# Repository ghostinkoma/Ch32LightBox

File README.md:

# LightBox — CH32V003 LED Dimmer Controller

**English** · [日本語](README_JP.md)

> **Status: ✅ Hardware Verified & Operational (as of 2026-09, no issues)** — All functions confirmed on both custom PCB (KiCad) and universal breadboard/perfboard. Verified nightlight, brightness control, soft start/off, 12-hour endurance test, and virtually zero heat generation with a ~1A LED.
> **Enclosed and currently in actual use inside a 3D-printed case designed in Fusion 360.**
>
> **License: Non-Commercial (CC BY-NC 4.0 compliant / Attribution required, modification allowed for non-commercial use, provided AS-IS without warranty)** → [LICENSE](LICENSE)

A single-channel PWM LED dimmer controlled via a rotary encoder.
Powered by the **CH32V003** microcontroller with a self-contained firmware based on [ch32fun](https://github.com/cnlohr/ch32fun).

To prioritize reproducing brightness as **perceived by the human eye**, the PWM duty cycle is generated using the **CIE 1931 L\* (lightness) curve**. One click produces a "perceptually equal" shift in brightness—slower changes at low levels and sharper changes at high levels—achieving a balanced response for human vision.

## Key Features

| Feature | Description |
|---|---|
| **CIE L\* Dimming** | Perceptually uniform brightness. 64 total steps, LUT generated at startup, runtime lookup via integer table. |
| **16-bit PWM** | TIM2, default 4095 steps / ~12 kHz. Adjustable resolution and frequency in `config.h`. |
| **Debouncing** | Full-step state machine (Ben Buxton) + direction reversal lockout (default 5 ms). No simple delays used. |
| **Fast-turn Snap** | Immediately sets duty to 100% or 0% if turned in the same direction $j$ times within $n$ ms. |
| **CW/CCW Support** | Swap rotation direction with a single line in `config.h`. |
| **Brightness Memory** | Flash wear leveling (dedicated 2 KB area, saved after 5 sec, ~1024x lifespan extension, saves ON/OFF state). |
| **Overheat Failsafe** (Default OFF) | Forcefully shuts off main PWM (MOSFET) when overheated → resumes when cooled down. Thermal throttles to $j$\% after $n$ cycles. **Die estimation disabled due to false triggers (`TEMP_PROTECT_ENABLE 0`)**; enable only when using an external NTC sensor. |
| **Watchdog** | IWDG. Automatically resets on system freeze for self-recovery. |
| **EMI Mitigation** | Configurable PWM slew rate (GPIO speed) + spread spectrum (period dithering, brightness invariant). |
| **Nightlight (WS2812 or single LED)** | When completely dark: ①WS2812/SK6812 breathes light↔dark on the CIE curve (RGB/RGBW, color order, max color), or ②a single-color LED blinks `x` ms every `n` s. |
| **Deep Low-Power (experimental)** | Optional battery mode (`LOW_POWER_MODE`): single-LED nightlight with the MCU in Standby between blinks (AWU periodic wake, push-switch EXTI wake). Default off; see CONFIG_REFERENCE. |
| **Soft Start** | Smoothly fades in/out to target brightness on power ON/OFF based on CIE curve (duration set in config, disabled if 0, max 65535 ms). |
| **Push Switch** | Short press toggles ON/OFF (time-based debouncing; smoothly tracks re-triggering during active fades). |

All configuration options are centralized in **`source/config.h`** (see [CONFIG_REFERENCE.md](documents/CONFIG_REFERENCE.md) for details).
Detailed specifications are in [SPEC.md](documents/SPEC.md), design decisions are in [DESIGN.md](documents/DESIGN.md), and battery / low-power and LED-driver notes are in [POWER_AND_DRIVER.md](documents/POWER_AND_DRIVER.md).

## Pinout (**All features fit on SOP8 / J4M6**)

| Pin | Signal | Function |
|---|---|---|
| PA1 | ENC_A | Encoder Phase A (Internal pull-up, Common=GND) |
| PC1 | ENC_B | Encoder Phase B (Internal pull-up, Common=GND) |
| PA2 | ENC_SW | Push Switch (Internal pull-up, Active Low) |
| PC2 | PWM | **Main LED Output** (default `PWM_PIN`=PC2 → TIM2_CH2 remap1) |
| PC4 | (Selectable) | **WS2812 Nightlight** / External Temp Sensor / Warning LED (Mutually exclusive, choose one) |
| PD1 | SWIO | Programming / debugprintf (Reserved) |

> **Feature ↔ pin assignment is done entirely in `config.h`** (one pin macro per feature: `PWM_PIN`, `ENC_*_PIN`, `WS_DIN_PIN`, `TEMP_SENSE_PIN`, `WARN_LED_PIN`). `source/pins.h` validates capabilities (PWM-/ADC-capable pins) and pin conflicts at compile time, and the LightBox Studio config editor mirrors the same checks. See the “Feature ↔ Pin Assignment” section of [CONFIG_REFERENCE.md](documents/CONFIG_REFERENCE.md).

> **Temperature protection is OFF by default** (die estimation rejected due to false shutdowns). Watchdog and EMI mitigations **require no external pins**, allowing PC4—the only remaining free pin on SOP8—to be used for the nightlight.
> If an external physical temperature sensor or warning LED is needed, allocate PC4 accordingly (mutually exclusive with the nightlight). To use more features simultaneously, switch to TSSOP20/QFN (F4P6) and assign individual pins in `config.h`.

## Connecting the LED

- **Recommended**: PC2 → MOSFET gate (e.g., AO3400 / 2N7002), driving the LED on the low side via the drain.
- **Simplified**: Low-current LEDs can be connected directly via `PC2 → [Resistor] → LED → GND` (Strictly respect $I_{\max} \approx 8\text{ mA}$ per pin).
- **Overheat Protection (Default OFF)**: The CH32V003 lacks an internal die temperature sensor. The initial duty-based "die temperature estimation" caused **false shutdowns (sudden turn-offs during continuous use)** because it was not a physical measurement. It has been **rejected (`TEMP_PROTECT_ENABLE 0`)**. If physical thermal protection is strictly required, attach a thermal-coupled NTC on the MOSFET to an ADC pin and run with `TEMP_PROTECT_ENABLE=1` + `TEMP_SOURCE=EXTERNAL`. See SPEC.md for details.

## Operation

- **Rotate Encoder**: $\pm 1$ step per click (perceptually equal spacing using CIE L*).
- **Fast Turn** (Default: 6+ clicks within 0.5s): Snaps to full brightness (100%) in the bright direction, or turns off (0%) in the dark direction.
- **Push Switch Short Press**: Toggles ON/OFF (retains last brightness level).
- **Auto Memory**: Defaults to 0 on first boot. Setting a brightness and leaving it untouched for 5 seconds automatically saves it to flash for next startup restoration.
- **Soft Start**: Fades in/out smoothly to target brightness on power ON/OFF or boot up (fade duration configured in config).
- **Nightlight**: Breathes automatically when turned completely dark (turns off when main LED turns on/brightens).

## Build & Flash

### ① ch32fun + Makefile (Verified Standard Build)

Dependencies: [ch32fun](https://github.com/cnlohr/ch32fun), RISC-V GCC (xpack riscv-none-elf recommended for `rv32ec libgcc`), WCH-LinkE.

```bash
cd source
make lightbox.bin CH32FUN=/path/to/ch32fun/ch32fun    # Build only
make             CH32FUN=/path/to/ch32fun/ch32fun    # Build -> Flash
```

Build memory footprints (Default config, all features ON, `DEBUG_LOG=0`): **Flash 8200 B / 16 KB (50%), RAM 184 B (9%)**.
Stripped footprint: Core only ~3 KB, + Nightlight ~3.6 KB. `DEBUG_LOG=1` adds ~1 KB.

> Set `DEBUG_LOG` to 1 only during development. `printf` is blocking and can stall if an SWD host is disconnected, causing dropped inputs in hot loops. Defaults to 0, which unlinks the printf infrastructure entirely.

### ② PlatformIO

See [PLATFORMIO.md](PLATFORMIO.md) (`platformio.ini` included).
*Note: The PlatformIO build has not been verified in this environment. The verified build method is the Makefile above.*

### ③ LightBox Studio (GUI — no VS Code required)

For a GUI-only workflow (`config.h` editing → compile → flash from a single menu), use the Java toolset in [tools/LightBoxStudio/](tools/LightBoxStudio/README.md). It downloads a self-contained toolchain on first run, so no command line or VS Code is required. See the [LightBox Studio README](tools/LightBoxStudio/README.md) for details.

## Directory Structure

```
LightBox/
├─ source/         Firmware source files
│  ├─ lightbox.c      Main application (main / encoder / PWM)
│  ├─ config.h        Centralized configuration (edit parameters here)
│  ├─ cie.h           CIE L* curve library (shared by main PWM & nightlight)
│  ├─ store.h         Non-volatile brightness storage (wear leveling)
│  ├─ temp.h          Temperature reading (external NTC, default OFF)
│  ├─ wdt.h           Watchdog timer (IWDG)
│  ├─ nightlight.h    WS2812/SK6812 nightlight driver
│  ├─ funconfig.h     ch32fun environment configuration
│  └─ Makefile
├─ documents/      SPEC.md / CONFIG_REFERENCE.md / HARDWARE.md / DESIGN.md / POWER_AND_DRIVER.md (+ *_JP.md)
├─ tools/          LightBoxStudio/ = GUI toolset (config edit → build → flash, no VS Code)
├─ ldscript/       Linker script for PlatformIO (lightbox_ch32v003.ld)
├─ PCB/            KiCad board files (LightBox/ = Schematic/PCB; AertWork.png; KiCad/ = FDS5680 lib)
├─ platformio.ini / PLATFORMIO.md
├─ 3D_Models/      Enclosure (Fusion 360 design / STL files, 3D printed)
└─ LICENSE         Non-commercial license (CC BY-NC 4.0 compliant)
```

## Enclosure

**Designed in Fusion 360 → 3D printed**. The board is assembled inside and **currently in operational use** (STL files available in `3D_Models/`).

## Hardware (PCB)

PCB layout, schematic, and artwork (with pin headers) completed → `PCB/LightBox/` (KiCad).
**Pin routing matches firmware exactly.** Details, BOM, and J1 pinout are in [HARDWARE.md](documents/HARDWARE.md).

- U1 CH32V003 (SOP8) / Q1 FDS5680 (N-MOSFET, low-side drive for main LED) / D1 SK6812 (OST45050C1A-W nightlight)
- R1 $100\ \Omega$ (Gate series resistor) / R2 $10\text{ k}\Omega$ (Gate pull-down = LED OFF during reset) / **D2 Pilot LED + R3 $100\ \Omega$ (series)**
- **Main (Power) LED is off-board** (Connected via LED OUT → J1). **Near-zero heat generation with ~1A LED** (heatsink added only as a precaution).
- J1 9-pin header: Breaks out Power / SWIO / Encoder / Signals for both LEDs. **Powered by $\text{VDD} = 5\text{ V}$**.
- Equivalent circuit constructed on a 1.27 mm pitch universal perfboard and verified working.

## Verification Status — ✅ Hardware Verified (Running Continuously)

- **★ Physical Board Operation Confirmed (2026-09-16 ~ present, running without issues)**: Board schematic/routing verified, flashing successful.
  - **Nightlight** (SK6812 / OST45050C1A-W, RGBW sequence)
  - **Brightness adjustment** (CIE L*, acceleration x3, fast-turn snap)
  - **ON/OFF soft start & soft off**
  - **12-hour ON / 12-hour OFF endurance test passed** (Disabling thermal protection eliminated false cutoffs, ensuring long-term stability)
- Build checks: Zero compiler warnings across all feature ON/OFF, RGBW, and half-step combinations (Makefile, ch32fun).
- Host simulation tests: CIE LUT, encoder state machine, flash wear store boundaries, nightlight curves, color ordering, acceleration, thermal model.
- Unverified: Long-term Flash wear (~10 million cycles by design), external NTC thermal protection (disabled by default), PlatformIO build environment.

## License

This project (original parts of firmware, PCB, enclosure, and documentation created by ghostinkoma) is licensed under a **Non-Commercial License (Creative Commons Attribution-NonCommercial 4.0 International / CC BY-NC 4.0 compliant)**. See [LICENSE](LICENSE) for full details.

- **Non-Commercial Use Only** (Contact the author for commercial licensing).
- **Attribution Required** (Must credit the original author **ghostinkoma** and "LightBox").
- **Modifications Allowed** (Free to adapt for non-commercial purposes; derivative works must inherit the same license conditions).
- **No Warranty / No Liability** (Provided "AS IS". The author accepts no responsibility for damages resulting from use).

*Note: Bundled/dependent third-party code (e.g., [ch32fun](https://github.com/cnlohr/ch32fun)) remains under its respective original licenses (MIT-x11 / NewBSD).*

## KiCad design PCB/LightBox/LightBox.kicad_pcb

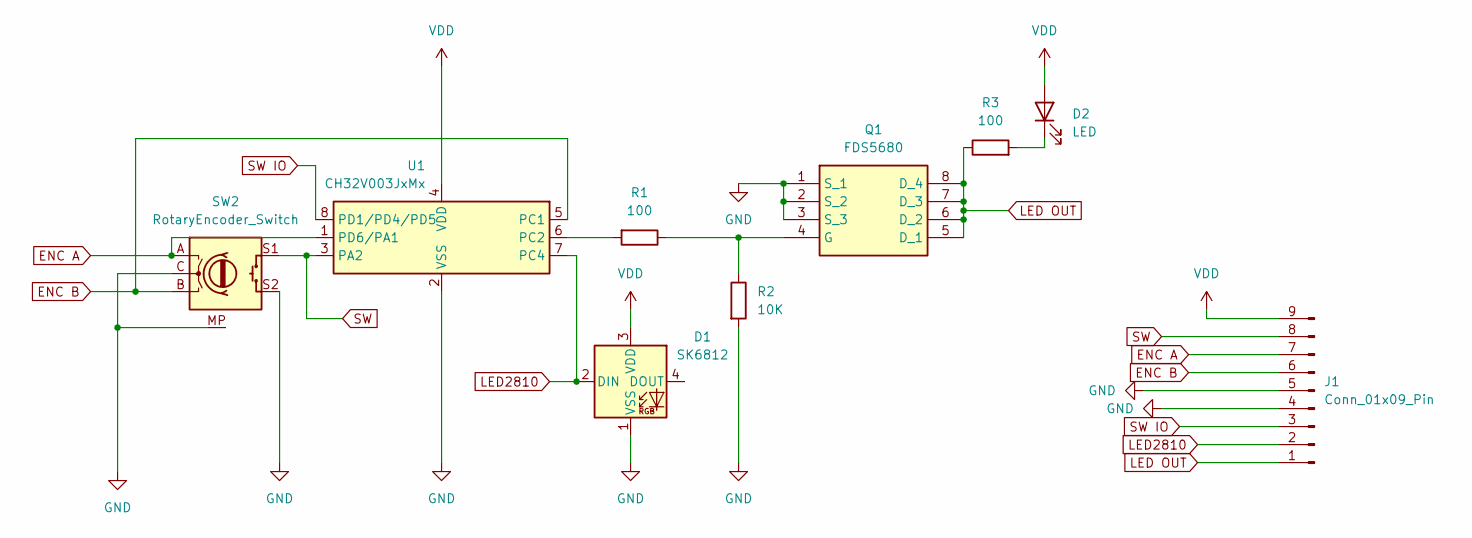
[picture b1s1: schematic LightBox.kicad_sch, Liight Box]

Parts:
D1: SK6812; LED_SK6812_PLCC4_5.0x5.0mm_P3.2mm
D2: LED; LED_D3.0mm
J1: Conn_01x09_Pin; PinHeader_1x09_P2.54mm_Vertical
Q1: FDS5680; SOIC-8-1EP_3.9x4.9mm_P1.27mm_EP2.29x3mm; Manufacturer_Part_Number FDS5680; Mouser Part Number 512-FDS5680
R1, R3: 100; R_0201_0603Metric
R2: 10K; R_0201_0603Metric
SW2: RotaryEncoder_Switch; RotaryEncoder_Alps_EC11E-Switch_Vertical_H20mm
U1: CH32V003JxMx; SOP-8_3.9x4.9mm_P1.27mm

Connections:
ENC A: J1.7, SW2.A, U1.1 (PD6/PA1)
ENC B: J1.6, SW2.B, U1.5 (PC1)
GND: D1.1 (VSS), J1.4, J1.5, Q1.1 (S_1), Q1.2 (S_2), Q1.3 (S_3), R2.2, SW2.C, SW2.MP, SW2.S2, U1.2 (VSS)
LED2810: D1.2 (DIN), J1.2, U1.7 (PC4)
LED OUT: J1.1, Q1.5 (D_1), Q1.6 (D_2), Q1.7 (D_3), Q1.8 (D_4), R3.1
unnamed: D2.1 (K), R3.2
unnamed: Q1.4 (G), R1.1, R2.1
unnamed: R1.2, U1.6 (PC2)
SW: J1.8, SW2.S1, U1.3 (PA2)
SW IO: J1.3, U1.8 (PD1/PD4/PD5)
VDD: D1.3 (VDD), D2.2 (A), J1.9, U1.4 (VDD)

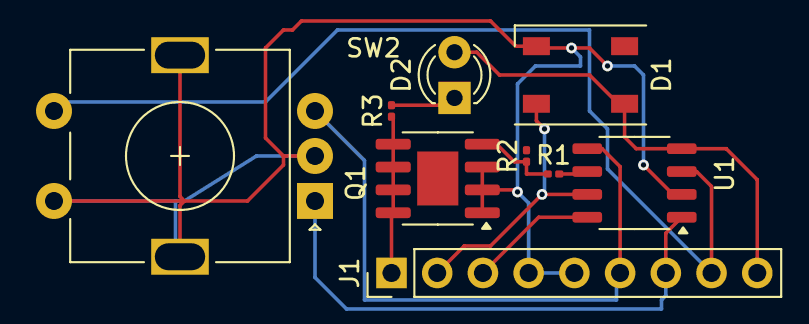
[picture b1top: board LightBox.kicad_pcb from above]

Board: 2 copper layers, 9 parts (0 on the bottom side), 11 nets.

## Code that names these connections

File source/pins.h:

/*
 * pins.h — 機能↔ピン割当の能力モデル・導出・コンパイル時検証 (CH32V003 SOP8 / J4M6)
 *
 *  config.h の「1機能=1ピンマクロ」から、各機能に必要な低レベル情報
 *  (GPIOポート/ピン番号 / ADCチャネル / PWMのタイマ・チャネル・remap) を導出し、
 *  ハード能力違反(PWM/ADC不可ピン)とピン衝突(2機能が同一ピン)をコンパイル時に弾く。
 *
 *  ── SOP8 (J4M6) の実在ピンと能力 ──  (出典: CH32V003 データシート / ch32fun ch32v003hw.h)
 *   pin   GPIO      ADCch   PWM経路(正出力)            既定用途
 *   PA1   GPIOA/1   1       TIM1_CH2 (no remap)        ENC_A
 *   PA2   GPIOA/2   0       (CH2N=相補のみ→PWM非対応)   ENC_SW
 *   PC1   GPIOC/1   -       TIM2_CH4 (remap1)          ENC_B
 *   PC2   GPIOC/2   -       TIM2_CH2 (remap1) ★既定PWM
 *   PC4   GPIOC/4   2       TIM1_CH4 (no remap)        常夜灯/温度/警告灯
 *   PD1   GPIOD/1   -       (CH3N=相補のみ) ※SWIO=書込/printf 予約
 *
 *  ※既定構成(PWM=PC2)は従来と同一のレジスタ操作を生成する(挙動不変)。
 *    PC2 以外の PWM ピンは「コンパイル対応・実機未検証」。
 */
#ifndef PINS_H
#define PINS_H

#include "ch32fun.h"   /* ピンマクロ(PA1=1,PC2=34,…) / GpioOf / TIM/RCC/AFIO 定義 */
#include "config.h"    /* 機能↔ピンの割当・有効フラグ */

/* ch32fun のピンマクロは整数値: 汎用の導出はビット演算で行える。
 *   GPIOポート = GpioOf(pin)  (= GPIOA_BASE + 0x400*(pin>>4))
 *   ピン番号   = (pin & 0x7)   (SOP8 は全て 0..7) */
#define LB_GPIO_OF(pin)   GpioOf(pin)
#define LB_PINNUM_OF(pin) ((pin) & 0x7)

/* SOP8 実在ピンか (それ以外は物理的に存在しない) */
#define LB_PIN_IS_SOP8(p) \
    ((p)==PA1 || (p)==PA2 || (p)==PC1 || (p)==PC2 || (p)==PC4 || (p)==PD1)

/* =========================================================================
 *  PWM 出力ピン → タイマ / チャネル / remap の導出
 *  正出力(単出力)チャネルのみ対応。相補(PA2=CH2N/PD1=CH3N)は既定除外。
 * ========================================================================= */
#if   PWM_PIN == PC2
  #define PWM_USES_TIM1    0
  #define PWM_CH           2
  #define PWM_REMAP_CLEAR  AFIO_PCFR1_TIM2_REMAP
  #define PWM_REMAP_SET    AFIO_PCFR1_TIM2_REMAP_PARTIALREMAP1
  #define PWM_RCC_GPIO_BIT RCC_APB2Periph_GPIOC
#elif PWM_PIN == PC1
  #define PWM_USES_TIM1    0
  #define PWM_CH           4
  #define PWM_REMAP_CLEAR  AFIO_PCFR1_TIM2_REMAP
  #define PWM_REMAP_SET    AFIO_PCFR1_TIM2_REMAP_PARTIALREMAP1
  #define PWM_RCC_GPIO_BIT RCC_APB2Periph_GPIOC
#elif PWM_PIN == PA1
  #define PWM_USES_TIM1    1
  #define PWM_CH           2
  #define PWM_REMAP_CLEAR  AFIO_PCFR1_TIM1_REMAP
  #define PWM_REMAP_SET    AFIO_PCFR1_TIM1_REMAP_NOREMAP
  #define PWM_RCC_GPIO_BIT RCC_APB2Periph_GPIOA
#elif PWM_PIN == PC4
  #define PWM_USES_TIM1    1
  #define PWM_CH           4
  #define PWM_REMAP_CLEAR  AFIO_PCFR1_TIM1_REMAP
  #define PWM_REMAP_SET    AFIO_PCFR1_TIM1_REMAP_NOREMAP
  #define PWM_RCC_GPIO_BIT RCC_APB2Periph_GPIOC
#else
  #error "PWM_PIN は PWM 可能な SOP8 ピンにしてください: PC2(TIM2_CH2)/PC1(TIM2_CH4)/PA1(TIM1_CH2)/PC4(TIM1_CH4)"
#endif

#if PWM_USES_TIM1
  #define PWM_TIMREG TIM1
#else
  #define PWM_TIMREG TIM2
#endif

#define PWM_GPIO_PORT  LB_GPIO_OF(PWM_PIN)
#define PWM_PINNUM     LB_PINNUM_OF(PWM_PIN)

/* チャネル番号(1..4)からレジスタ/ビットを合成する2段展開マクロ */
#define LB_CVR_(t,c)   ((t)->CH##c##CVR)
#define LB_CVR(t,c)    LB_CVR_(t,c)
#define PWM_CVR        LB_CVR(PWM_TIMREG, PWM_CH)                 /* 比較値レジスタ */

#define LB_OCM_(c)     (TIM_OC##c##M_2 | TIM_OC##c##M_1 | TIM_OC##c##PE) /* PWM mode1 + preload */
#define LB_OCM(c)      LB_OCM_(c)
#define PWM_OCM        LB_OCM(PWM_CH)

#define LB_CCE_(c)     (TIM_CC##c##E)                            /* 出力有効 */
#define LB_CCE(c)      LB_CCE_(c)
#define PWM_CCE        LB_CCE(PWM_CH)

/* CH1/CH2 は CHCTLR1、CH3/CH4 は CHCTLR2 に OCxM を書く */
#if PWM_CH <= 2
  #define PWM_CHCTLR   PWM_TIMREG->CHCTLR1
#else
  #define PWM_CHCTLR   PWM_TIMREG->CHCTLR2
#endif

/* =========================================================================
 *  外付け温度センサ(ADC) ピン → ADCチャネルの導出 (external 使用時のみ)
 * ========================================================================= */
#if TEMP_PROTECT_ENABLE && (TEMP_SOURCE == TEMP_SOURCE_EXTERNAL)
  #if   TEMP_SENSE_PIN == PA2
    #define TEMP_ADC_CH 0
  #elif TEMP_SENSE_PIN == PA1
    #define TEMP_ADC_CH 1
  #elif TEMP_SENSE_PIN == PC4
    #define TEMP_ADC_CH 2
  #else
    #error "TEMP_SENSE_PIN は ADC 対応の SOP8 ピンにしてください: PA2(ch0)/PA1(ch1)/PC4(ch2)"
  #endif
#endif

/* =========================================================================
 *  常夜灯 WS2812 データピン → GPIOポート/ピン番号の導出
 * ========================================================================= */
#define WS_GPIO_PORT   LB_GPIO_OF(WS_DIN_PIN)
#define WS_GPIO_PINNUM LB_PINNUM_OF(WS_DIN_PIN)

/* =========================================================================
 *  ピン衝突検出 (全機能横断・コンパイル時)
 *    各 SOP8 ピンに一意ビットを割当て、有効な機能だけが自分のピンビットを寄与する
 *    「加算(SUM)」と「論理和(OR)」を作る。重複があれば加算で桁上がりして SUM!=OR に
 *    なる → _Static_assert で検出。ビットは数値ピンIDで引く(マクロは整数に展開される)。
 * ========================================================================= */
#define PIN_BIT_1   (1u << 0)   /* PA1 */
#define PIN_BIT_2   (1u << 1)   /* PA2 */
#define PIN_BIT_33  (1u << 2)   /* PC1 */
#define PIN_BIT_34  (1u << 3)   /* PC2 */
#define PIN_BIT_36  (1u << 4)   /* PC4 */
#define PIN_BIT_49  (1u << 5)   /* PD1 */
#define LB_PINBIT_(p) PIN_BIT_##p
#define LB_PINBIT(p)  LB_PINBIT_(p)   /* p は数値に展開されてから貼付 (PA1→1→PIN_BIT_1) */

/* 常に使うピン: エンコーダ A/B/SW と 本体 PWM */
#define LB_BITS_ALWAYS_SUM \
    (LB_PINBIT(ENC_A_PIN) + LB_PINBIT(ENC_B_PIN) + LB_PINBIT(ENC_SW_PIN) + LB_PINBIT(PWM_PIN))
#define LB_BITS_ALWAYS_OR  \
    (LB_PINBIT(ENC_A_PIN) | LB_PINBIT(ENC_B_PIN) | LB_PINBIT(ENC_SW_PIN) | LB_PINBIT(PWM_PIN))

/* 任意機能: 有効なときだけピンビットを寄与 */
#if NIGHTLIGHT_ENABLE
  #if NIGHTLIGHT_TYPE == NL_TYPE_SINGLE
    #define LB_NL_PIN NL_LED_PIN      /* 単色LED常夜灯の専用ピン */
  #else
    #define LB_NL_PIN WS_DIN_PIN      /* WS2812 データピン */
  #endif
  #define LB_BIT_NL LB_PINBIT(LB_NL_PIN)
#else
  #define LB_BIT_NL 0u
#endif
#if TEMP_PROTECT_ENABLE && (TEMP_SOURCE == TEMP_SOURCE_EXTERNAL)
  #define LB_BIT_TEMP LB_PINBIT(TEMP_SENSE_PIN)
#else
  #define LB_BIT_TEMP 0u
#endif
#if WARN_LED_ENABLE
  #define LB_BIT_WARN LB_PINBIT(WARN_LED_PIN)
#else
  #define LB_BIT_WARN 0u
#endif

#define LB_USED_SUM (LB_BITS_ALWAYS_SUM + LB_BIT_NL + LB_BIT_TEMP + LB_BIT_WARN)
#define LB_USED_OR  (LB_BITS_ALWAYS_OR  | LB_BIT_NL | LB_BIT_TEMP | LB_BIT_WARN)

/* 能力・存在チェック(分かりやすいメッセージを先に出す) */
_Static_assert(LB_PIN_IS_SOP8(ENC_A_PIN),  "ENC_A_PIN は SOP8 ピン(PA1/PA2/PC1/PC2/PC4/PD1)にしてください");
_Static_assert(LB_PIN_IS_SOP8(ENC_B_PIN),  "ENC_B_PIN は SOP8 ピンにしてください");
_Static_assert(LB_PIN_IS_SOP8(ENC_SW_PIN), "ENC_SW_PIN は SOP8 ピンにしてください");
_Static_assert(LB_PIN_IS_SOP8(PWM_PIN),    "PWM_PIN は SOP8 ピンにしてください");
#if NIGHTLIGHT_ENABLE
_Static_assert(LB_PIN_IS_SOP8(LB_NL_PIN), "nightlight pin (WS_DIN_PIN / NL_LED_PIN) must be a SOP8 pin");
#endif
#if WARN_LED_ENABLE
_Static_assert(LB_PIN_IS_SOP8(WARN_LED_PIN), "WARN_LED_PIN は SOP8 ピンにしてください");
#endif

/* 衝突検出: 2機能が同一ピンなら SUM!=OR
 * (メッセージは ASCII 先頭。日本語は gcc が8進エスケープ表示するため識別語を前置) */
_Static_assert(LB_USED_SUM == LB_USED_OR,
    "LightBox PIN CONFLICT: two features are assigned to the same pin. "
    "Fix the pin assignments in config.h (PWM_PIN/ENC_*_PIN/WS_DIN_PIN/TEMP_SENSE_PIN/WARN_LED_PIN).");

/* SWIO(PD1) は書込/printf 用の予約ピン。機能割当は非推奨(警告のみ) */
#if (ENC_A_PIN==PD1)||(ENC_B_PIN==PD1)||(ENC_SW_PIN==PD1)||(PWM_PIN==PD1)|| \
    (NIGHTLIGHT_ENABLE && (LB_NL_PIN==PD1))|| \
    (WARN_LED_ENABLE && (WARN_LED_PIN==PD1))|| \
    (TEMP_PROTECT_ENABLE && (TEMP_SOURCE==TEMP_SOURCE_EXTERNAL) && (TEMP_SENSE_PIN==PD1))
  #warning "PD1 は SWIO(書込/debugprintf)予約ピンです。機能割当は書込/デバッグと競合します"
#endif

#endif /* PINS_H */
